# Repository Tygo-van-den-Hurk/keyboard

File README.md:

> This repository will be used for making of my first custom keyboard.

<br>
<center>
  <!--~ Tools ~-->

  <!--~ CI/CD ~-->

  <!--~ Repository Statistics ~-->

</center>
<br>

# Keyboard

- [Keyboard](#keyboard)
  - [Overview](#overview)
  - [Documentation](#documentation)
  - [Credits](#credits)

## Overview

So this repository is for the journey of me making my first keyboard: _Snowflake_. I wanted a keyboard that works for me, I wanted something that I could take with me anywhere and would work the way I designed it to do. This also was a good excuse to learn about keyboards which is something I've wanted to do for a while now.

## Documentation

There are two parts to this journey: [hardware](./hardware/README.md), and [software](./software/README.md). You can learn more in their respective documentation submodules. If you need to know anything else and it's not in the docs you can open a issue or even PR and I'll fix/add it.

## Credits

This code is written by, or using the help of:

- [@Narkoleptika](https://github.com/Narkoleptika) for providing the pro micro footprint and setting me up with a template.
- [@RajuBuddharaju](https://github.com/RajuBuddharaju) for helping me realise every part of this keyboard.
- [@Tygo-van-den-Hurk](https://github.com/Tygo-van-den-Hurk)

To see how to start or develop see [CONTRIBUTING.md](./CONTRIBUTING.md).

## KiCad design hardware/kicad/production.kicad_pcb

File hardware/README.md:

> This submodule is for generating the hardware of my keyboard.

[< Back to the main README](../README.md)

# Hardware

- [Hardware](#hardware)
  - [Overview](#overview)
  - [Kicad](#kicad)
  - [Ergogen](#ergogen)
    - [Adding custom footprints](#adding-custom-footprints)
  - [External Resources](#external-resources)
  - [Components](#components)

## Overview

For the generating the files we need for the hardware we'll be using [ergogen](https://github.com/ergogen/ergogen). [Ergogen](https://github.com/ergogen/ergogen) is a program that allows you to build keyboards from a YAML config file.

## Kicad

Kicad is used for adding the wires to a PCB. Unfortunately every time you update the PCB you'll have to rewire it yourself. So far I've seen no way to do that manually. To update the PCB run:

```SH
nix run .#update-pcb
```

We keep the pcb files in the kicad folder to be tracked by version control. Since these are text files and not binary these are really easy to add to version control. If you are developing and you want rapid updates to your PCB, you can run:

```SH
nix run .#watch-pcb
```

to automatically update the PCB on any changes.

## Ergogen

We use ergogen to build the hardware. Ergogen builds: the PCBs, outlines, cases, and points. To build any of it use:

```SH
nix build .#pcbs
nix build .#outlines
nix build .#cases
nix build .#points
```

to build any of them. You can also get in a dev shell with ergogen using `nix develop` and then run ergogen manually.

### Adding custom footprints

There is just one problem: Ergogen does not natively support the pro micro I want to use for my keyboard. So to solve this we have to use footprints. Footprints is a way to extend ergogen's functionality beyond it's native capabilities.

To use footprints we have to use the following structure: there has to be a directory called `footprints` and a file called `config.yaml`. The `config.yaml` is where we'll describe our keyboard to ergogen, and in the `footprints` folder we'll put our missing footprints. Thanks to [@Narkoleptika](https://github.com/Narkoleptika)'s hard work (or who ever he got it from) there is a footprint for the pro micro.

If you need any footprint that this repository is missing, you can find it's JavaScript file, and add it to the `./src/footprints/` directory. There are a lot of footprints you can use. Just make sure it's well tested, because a bad footprint could technically destroy your microcontroller.

## External Resources

- [The ergogen docs](https://docs.ergogen.xyz/) for any questions about how ergogen works.
- [Web-based deployments](https://ergogen.ceoloide.com/) for getting a visual impression of what the keys look like.
- [The ergogen v4 guid I used](https://flatfootfox.com/ergogen-introduction/) for a step by step tutorial.

## Components

Here are the components I used for my keyboard:

- Choc key switches
- a `pro micro` micro controller
- my self made PCB

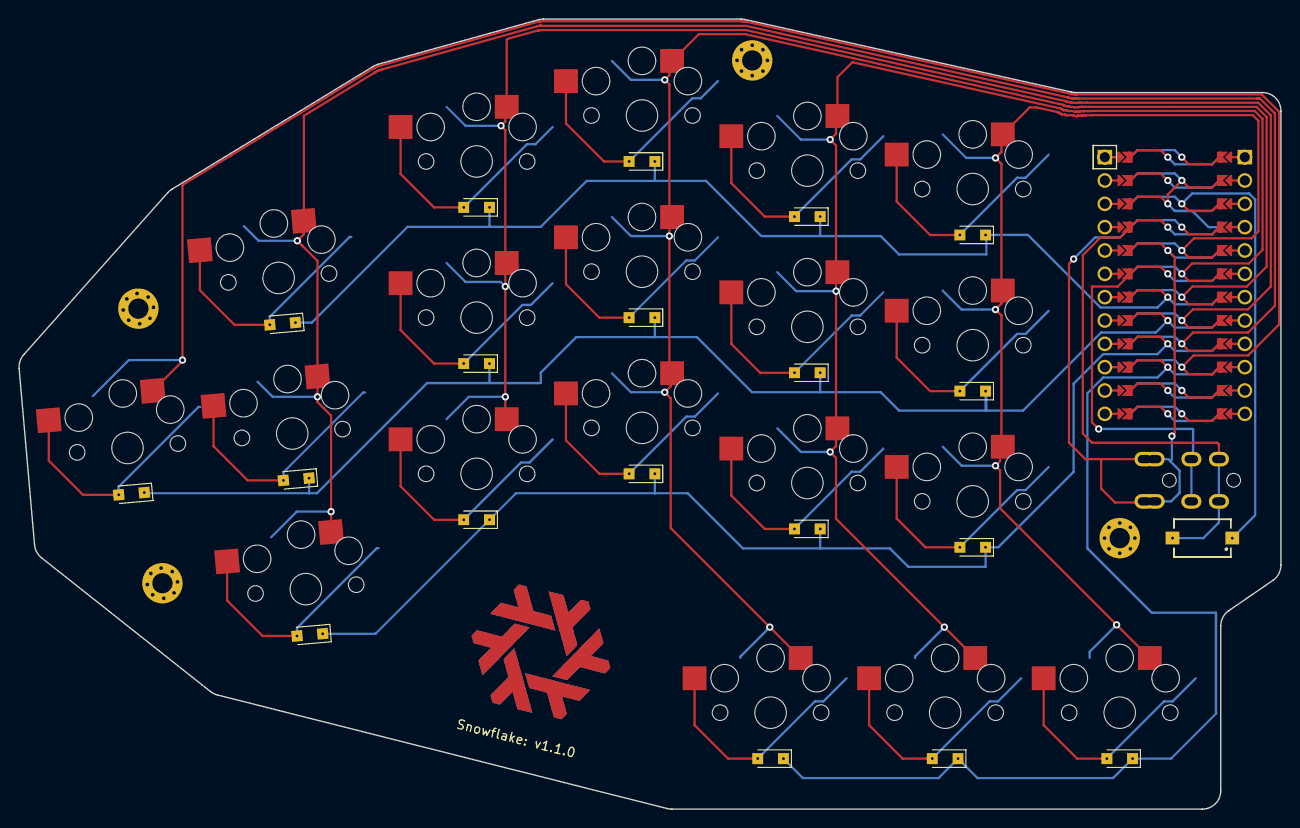
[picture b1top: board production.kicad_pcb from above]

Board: 2 copper layers, 137.4 x 86.0 mm, 45 parts (0 on the bottom side), 34 nets.

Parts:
D1, D2, D3, D4, D5, D6, D7, D8, D9, D10, D11, D12, D13, D14, D15, D16, D17, D18, D19: Nexperia_CFP3_SOD-123W
MCU1: ProMicro
S1, S2, S3, S4, S5, S6, S7, S8, S9, S10, S11, S12, S13, S14, S15, S16, S17, S18, S19: PG1350
S20: 434121025816
TRRS1: TRRS-PJ-320A-dual
_1, _2, _3, _4: MountingHole_2.2mm_M2_Pad_Via

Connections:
GND: MCU1.2, MCU1.21, MCU1.22, S20.2, TRRS1.4
P2: MCU1.20, TRRS1.2
P3: MCU1.19, TRRS1.3
P4: D4.1, D7.1, D10.1, D13.1, D16.1, MCU1.18
P5: D1.1, D3.1, D6.1, D9.1, D12.1, D15.1, MCU1.17
P6: D2.1, D5.1, D8.1, D11.1, D14.1, MCU1.16
P7: D17.1, D18.1, D19.1, MCU1.15
P14: MCU1.10, S1.1
P15: MCU1.9, S2.1, S3.1, S4.1
P18: MCU1.8, S5.1, S6.1, S7.1
P19: MCU1.7, S8.1, S9.1, S10.1, S17.1
P20: MCU1.6, S11.1, S12.1, S13.1, S18.1
P21: MCU1.5, S14.1, S15.1, S16.1, S19.1
RST: MCU1.3, S20.1
VCC: MCU1.4, TRRS1.1
matrix_index_bottom: D11.2, S11.2
matrix_index_home: D12.2, S12.2
matrix_index_top: D13.2, S13.2
matrix_inner_bottom: D14.2, S14.2
matrix_inner_home: D15.2, S15.2
matrix_inner_top: D16.2, S16.2
matrix_middle_bottom: D8.2, S8.2
matrix_middle_home: D9.2, S9.2
matrix_middle_top: D10.2, S10.2
matrix_outer_home: D1.2, S1.2
matrix_pinky_bottom: D2.2, S2.2
matrix_pinky_home: D3.2, S3.2
matrix_pinky_top: D4.2, S4.2
matrix_ring_bottom: D5.2, S5.2
matrix_ring_home: D6.2, S6.2
matrix_ring_top: D7.2, S7.2
thumbfan_far_thumb: D19.2, S19.2
thumbfan_home_thumb: D18.2, S18.2
thumbfan_near_thumb: D17.2, S17.2

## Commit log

2024-11-16 Added ergogen raw input yaml.
2024-11-16 Updated the README with the basic notes.
2024-11-16 Added an outer key to the sides.
2024-11-17 Updated the README.md to have a basic step by step plan of how to build the keyboard.
2024-12-14 Added outline, and adjusted some parameters
2024-12-21 Made a flake file for creating a reproducable shell.
2024-12-21 Added ergogen as a submodule for generating the files locally.
2024-12-21 Added a make file to make commands reproducable.
2024-12-21 Added '.gitignore' to ignore the output and wiring directories. These should be deterministically reporducable thanks to Nix.
2024-12-21 Added a schematic of what the collumns and rows should look like.
2024-12-21 Added a PCB section to generate PCBs.
2024-12-21 Added the PCB folder for Kicad PCBs.
2024-12-21 Added footprints to the PCB.
2025-01-18 Updated the README to be my own.
2025-01-18 Copied the flake over from the old repo.
2025-01-18 Copied the 'Makefile' over from the old repo
2025-01-18 Copied my config over from the old repo
2025-01-18 Ran 'npm install'.
2025-02-16 Ignoring autosave files from kicad.
2025-02-16 Changed the watch script to use my make file.
2025-02-16 Added an image to show how the rows and collums are defined.
2025-02-17 Ignoring all types of caches and backups from kicad
2025-02-17 Updated package.json to have my name and URLs.
2025-02-17 Added a Nix icon to ergogen to put onto the PCB.
2025-02-17 Did wiring and made PCB.
2025-02-17 Found another file that kicad produces I don't wish to be able to accidentally commit.
2025-02-17 Updated the PCB
2025-02-17 Added metadata such as the author to the config and PCBs.
2025-02-24 Removed a useless comment.
2025-02-24 Made the nix piece be on both sides.
2025-03-22 Changed license from 'MIT' to 'ELP-2.0'.
2025-04-18 Named the keyboard 'Snowflake'.
2025-04-18 Made 'Makefile' lowercase
2025-04-18 Did wiring for 'v1.0.0'.
2025-04-22 Moved the ergogen PCB thing into the flake.
2025-04-22 Added a dev container
2025-04-22 Added the nix flake check and github deployment workflows.
2025-04-22 Renamed 'zmk' to 'software'
2025-04-22 moved everything into the flake, so now the package.json is no longer needed.
2025-04-22 Removed unused footprints.
2025-04-22 Updated the documentation.
2025-04-22 Renamed the devcontainer
2025-04-22 Fixed 'nix flake check' CI/CD.
2025-04-22 Tempararily only checking linux-86x_64.
2025-04-24 Made the switch keys reversable.
2025-04-25 Fixed main issue with v.1.0.0: Made switches reversable
    - Added 'nix run .#watch-pcb' command.
    - made switches reverseable
    - rewired
2025-04-25 Made GH pages deploy only run on changes to Markdown files as that's the only thing they rely on.
2025-05-05 Added formatters
2025-05-05 Applied nix formatter.
2025-05-05 Added none-flake compatibility layer.
2025-05-05 Formatted
2025-05-05 Added '.envrc' for direnv.
2025-05-05 Added editor config
2025-05-05 Made line endings consistant.
2025-05-05 Made flake less verbose.
2025-05-05 Updated documentation
2025-05-05 Wiped software from what was pre-configured by @Narkoleptika.
2025-05-05 Formatted.
2025-05-05 Split up devshell into software and hardware.
2025-05-05 Added 'CONTRIBUTING.md' for more information about how to contribute.
2025-05-05 Added dependabot file for keeping workflows up to date.
2025-05-05 Added workflows that greets new contributers.
2025-05-05 Added workflow that checks all files for the naming conventions.
2025-05-05 Formatted 'flake.nix'.
2025-05-05 Updated the README
2025-05-05 Bump cachix/install-nix-action from 30 to 31
    Bumps [cachix/install-nix-action](https://github.com/cachix/install-nix-action) from 30 to 31.
    - [Release notes](https://github.com/cachix/install-nix-action/releases)
    - [Changelog](https://github.com/cachix/install-nix-action/blob/master/RELEASE.md)
    - [Commits](https://github.com/cachix/install-nix-action/compare/v30...v31)
    ---
    updated-dependencies:
2025-05-05 Bump actions/checkout from 3 to 4
    Bumps [actions/checkout](https://github.com/actions/checkout) from 3 to 4.
    - [Release notes](https://github.com/actions/checkout/releases)
    - [Changelog](https://github.com/actions/checkout/blob/main/CHANGELOG.md)
    - [Commits](https://github.com/actions/checkout/compare/v3...v4)
    ---
    updated-dependencies:
2025-05-05 Added mounting holes and improved switches from 'github:ceoloide/ergogen-footprints'.
2025-05-05 Added mounting holes.
2025-05-05 Updated the version on the keyboard after adding mounting holes.
2025-05-05 Added drill and gerber files to the git ignore list.
2025-05-05 Removed assets as I no longer need them.
2025-05-05 Changed the pin out to be easier to wire.
2025-05-05 wired the keyboard
2025-05-05 Added a VS code folder for suggestions for extentions.
2025-05-05 Added nix pre-commmit support.

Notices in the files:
README.md:
The Eclipse Public License v2.0 badge
